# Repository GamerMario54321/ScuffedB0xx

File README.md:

# ScuffedB0xx
A pcb for the B0xx layout that uses the pico.

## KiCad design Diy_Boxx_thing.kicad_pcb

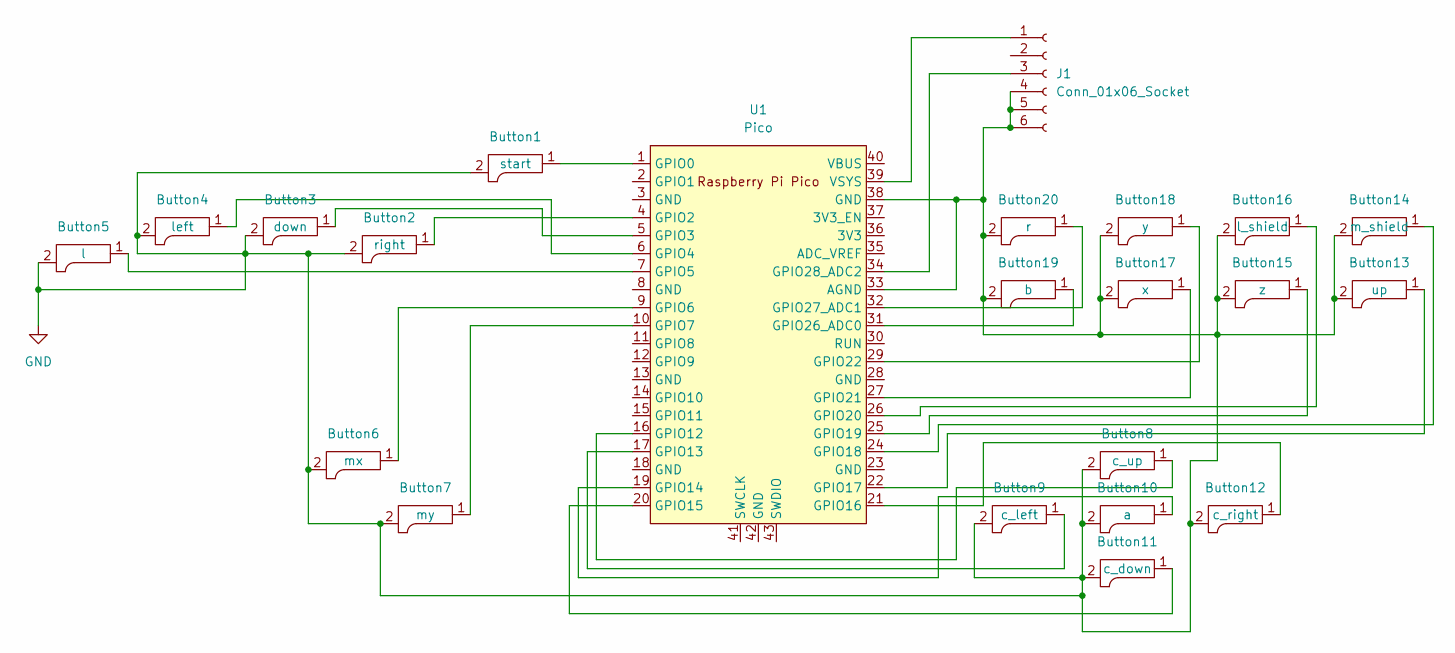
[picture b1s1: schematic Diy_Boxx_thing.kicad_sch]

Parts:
Button1: start; Kailh_socket_MX
Button2: right; Kailh_socket_MX
Button3: down; Kailh_socket_MX
Button4: left; Kailh_socket_MX
Button5: l; Kailh_socket_MX
Button6: mx; Kailh_socket_MX
Button7: my; Kailh_socket_MX
Button8: c_up; Kailh_socket_MX
Button9: c_left; Kailh_socket_MX
Button10: a; Kailh_socket_MX
Button11: c_down; Kailh_socket_MX
Button12: c_right; Kailh_socket_MX
Button13: up; Kailh_socket_MX
Button14: m_shield; Kailh_socket_MX
Button15: z; Kailh_socket_MX
Button16: l_shield; Kailh_socket_MX
Button17: x; Kailh_socket_MX
Button18: y; Kailh_socket_MX
Button19: b; Kailh_socket_MX
Button20: r; Kailh_socket_MX
J1: Conn_01x06_Socket; PinSocket_1x06_P2.00mm_Vertical
U1: Pico; RPi_Pico_SMD_TH

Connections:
GND: Button1.2, Button2.2, Button3.2, Button4.2, Button5.2, Button6.2, Button7.2, Button8.2, Button9.2, Button10.2, Button11.2, Button12.2, Button13.2, Button14.2, Button15.2, Button16.2, Button17.2, Button18.2, Button19.2, Button20.2, J1.4, J1.5, J1.6, U1.33 (AGND), U1.38 (GND)
unnamed: J1.1, U1.39 (VSYS)
unnamed: J1.3, U1.34 (GPIO28_ADC2)
unnamed: Button1.1, U1.1 (GPIO0)
unnamed: Button2.1, U1.4 (GPIO2)
unnamed: Button3.1, U1.5 (GPIO3)
unnamed: Button4.1, U1.6 (GPIO4)
unnamed: Button5.1, U1.7 (GPIO5)
unnamed: Button6.1, U1.9 (GPIO6)
unnamed: Button7.1, U1.10 (GPIO7)
unnamed: Button8.1, U1.16 (GPIO12)
unnamed: Button9.1, U1.17 (GPIO13)
unnamed: Button10.1, U1.19 (GPIO14)
unnamed: Button11.1, U1.20 (GPIO15)
unnamed: Button12.1, U1.21 (GPIO16)
unnamed: Button13.1, U1.22 (GPIO17)
unnamed: Button14.1, U1.24 (GPIO18)
unnamed: Button15.1, U1.25 (GPIO19)
unnamed: Button16.1, U1.26 (GPIO20)
unnamed: Button17.1, U1.27 (GPIO21)
unnamed: Button18.1, U1.29 (GPIO22)
unnamed: Button19.1, U1.31 (GPIO26_ADC0)
unnamed: Button20.1, U1.32 (GPIO27_ADC1)

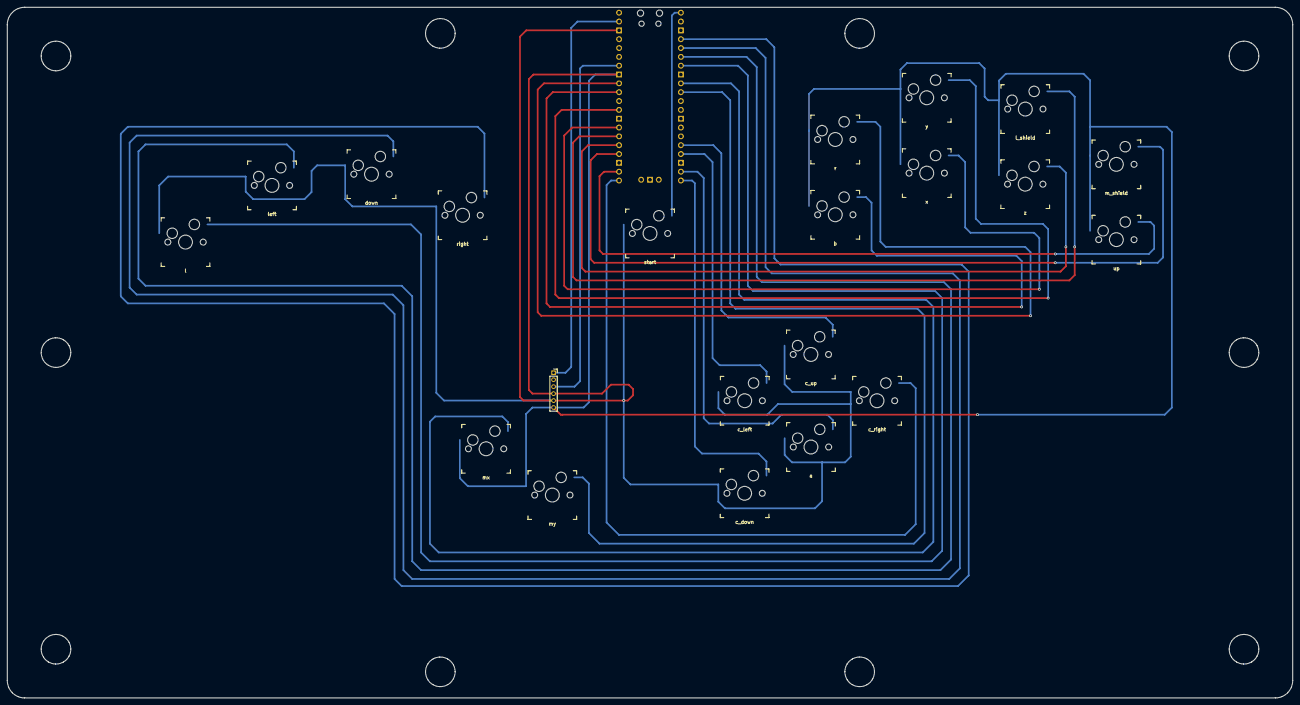
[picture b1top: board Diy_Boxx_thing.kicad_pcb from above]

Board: 2 copper layers, 369.6 x 198.6 mm, 22 parts (1 on the bottom side), 23 nets.
